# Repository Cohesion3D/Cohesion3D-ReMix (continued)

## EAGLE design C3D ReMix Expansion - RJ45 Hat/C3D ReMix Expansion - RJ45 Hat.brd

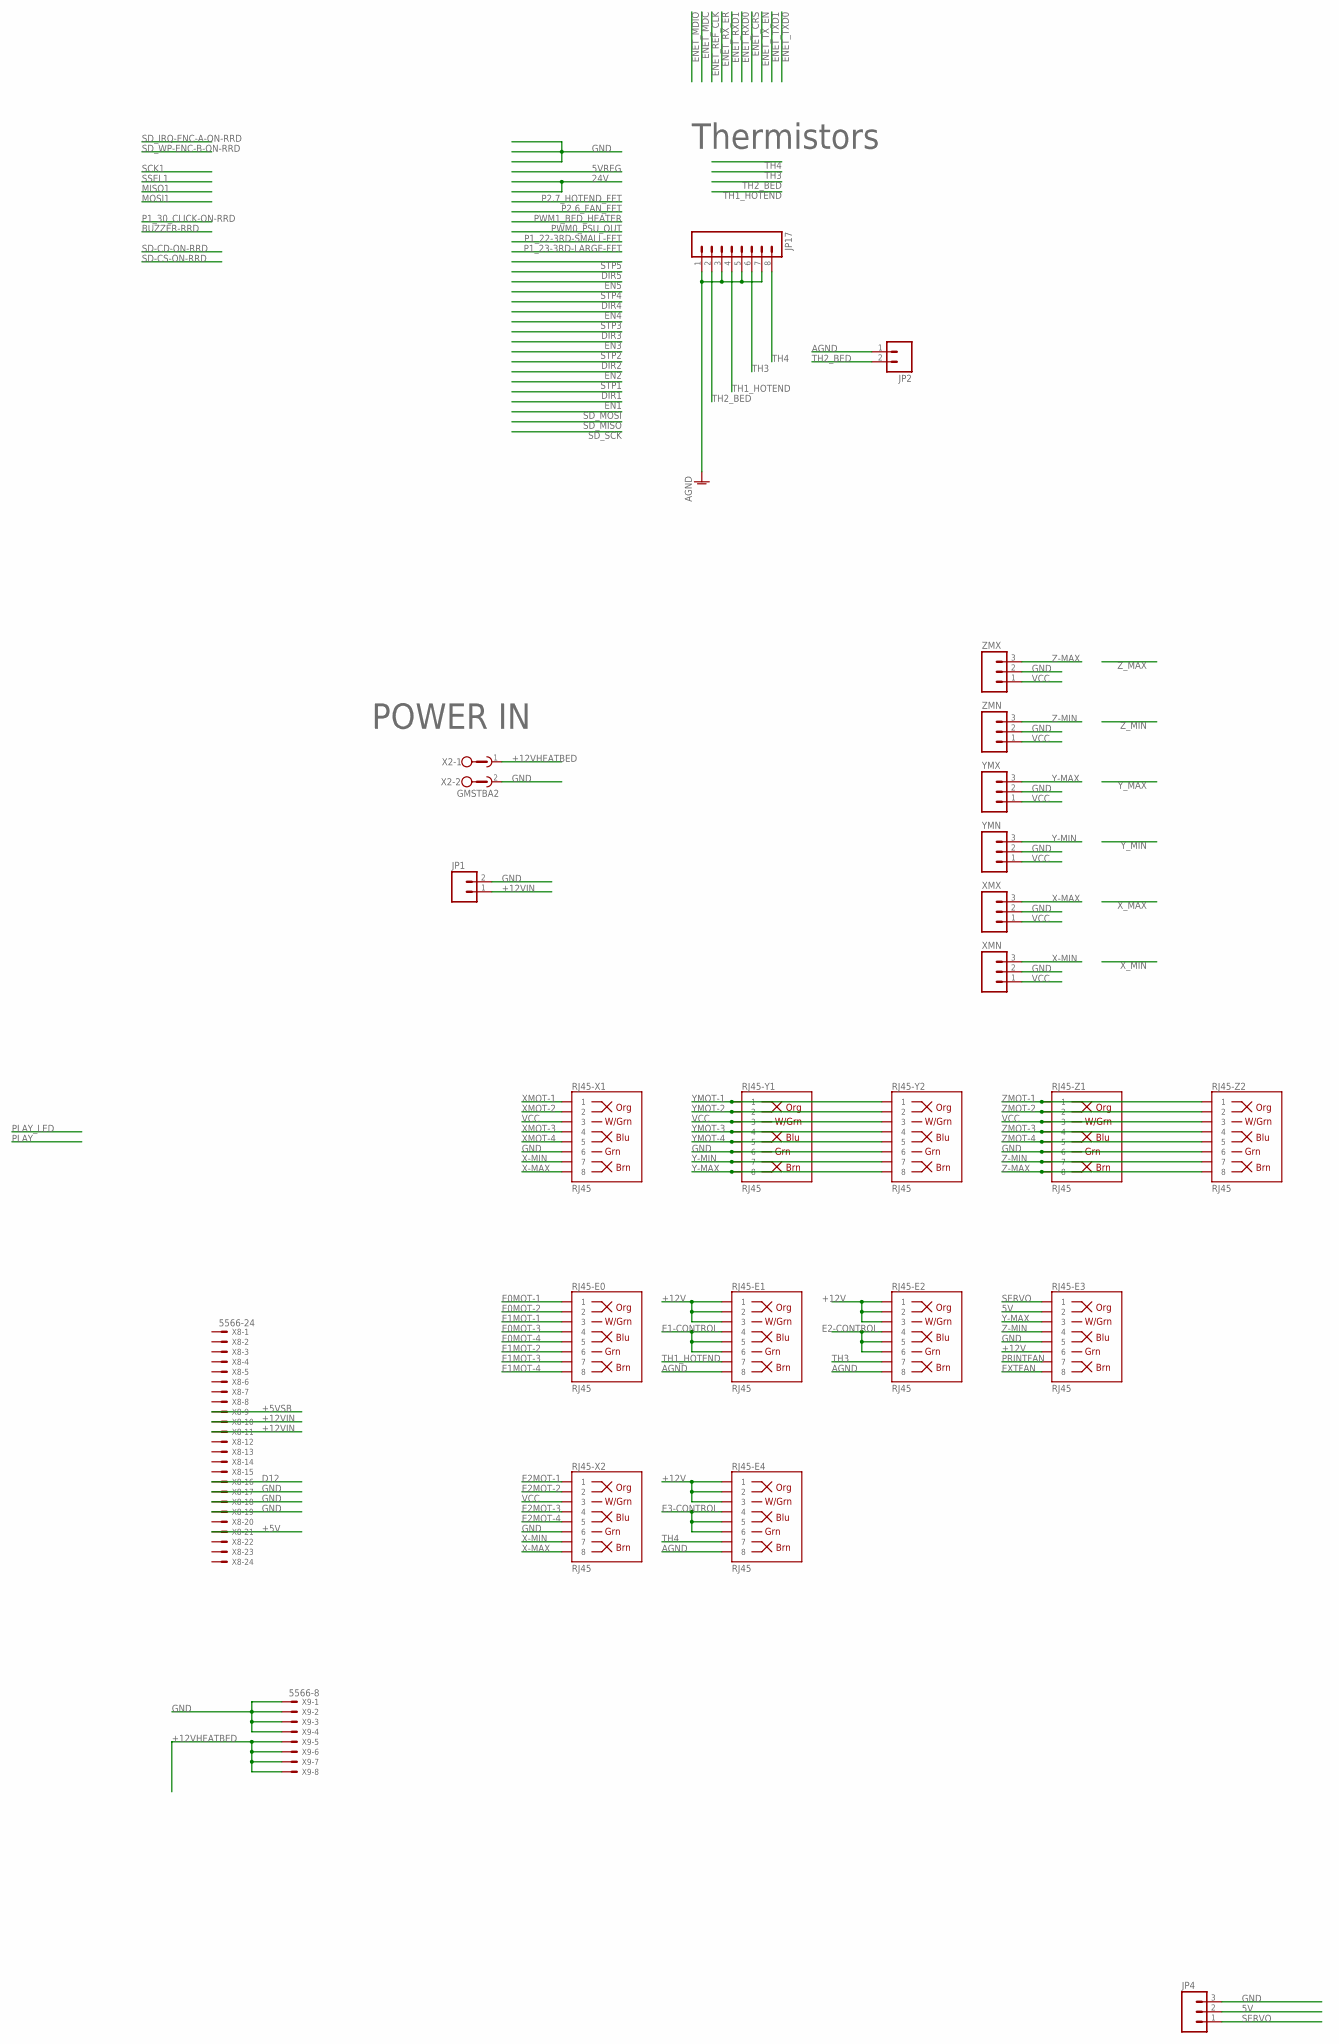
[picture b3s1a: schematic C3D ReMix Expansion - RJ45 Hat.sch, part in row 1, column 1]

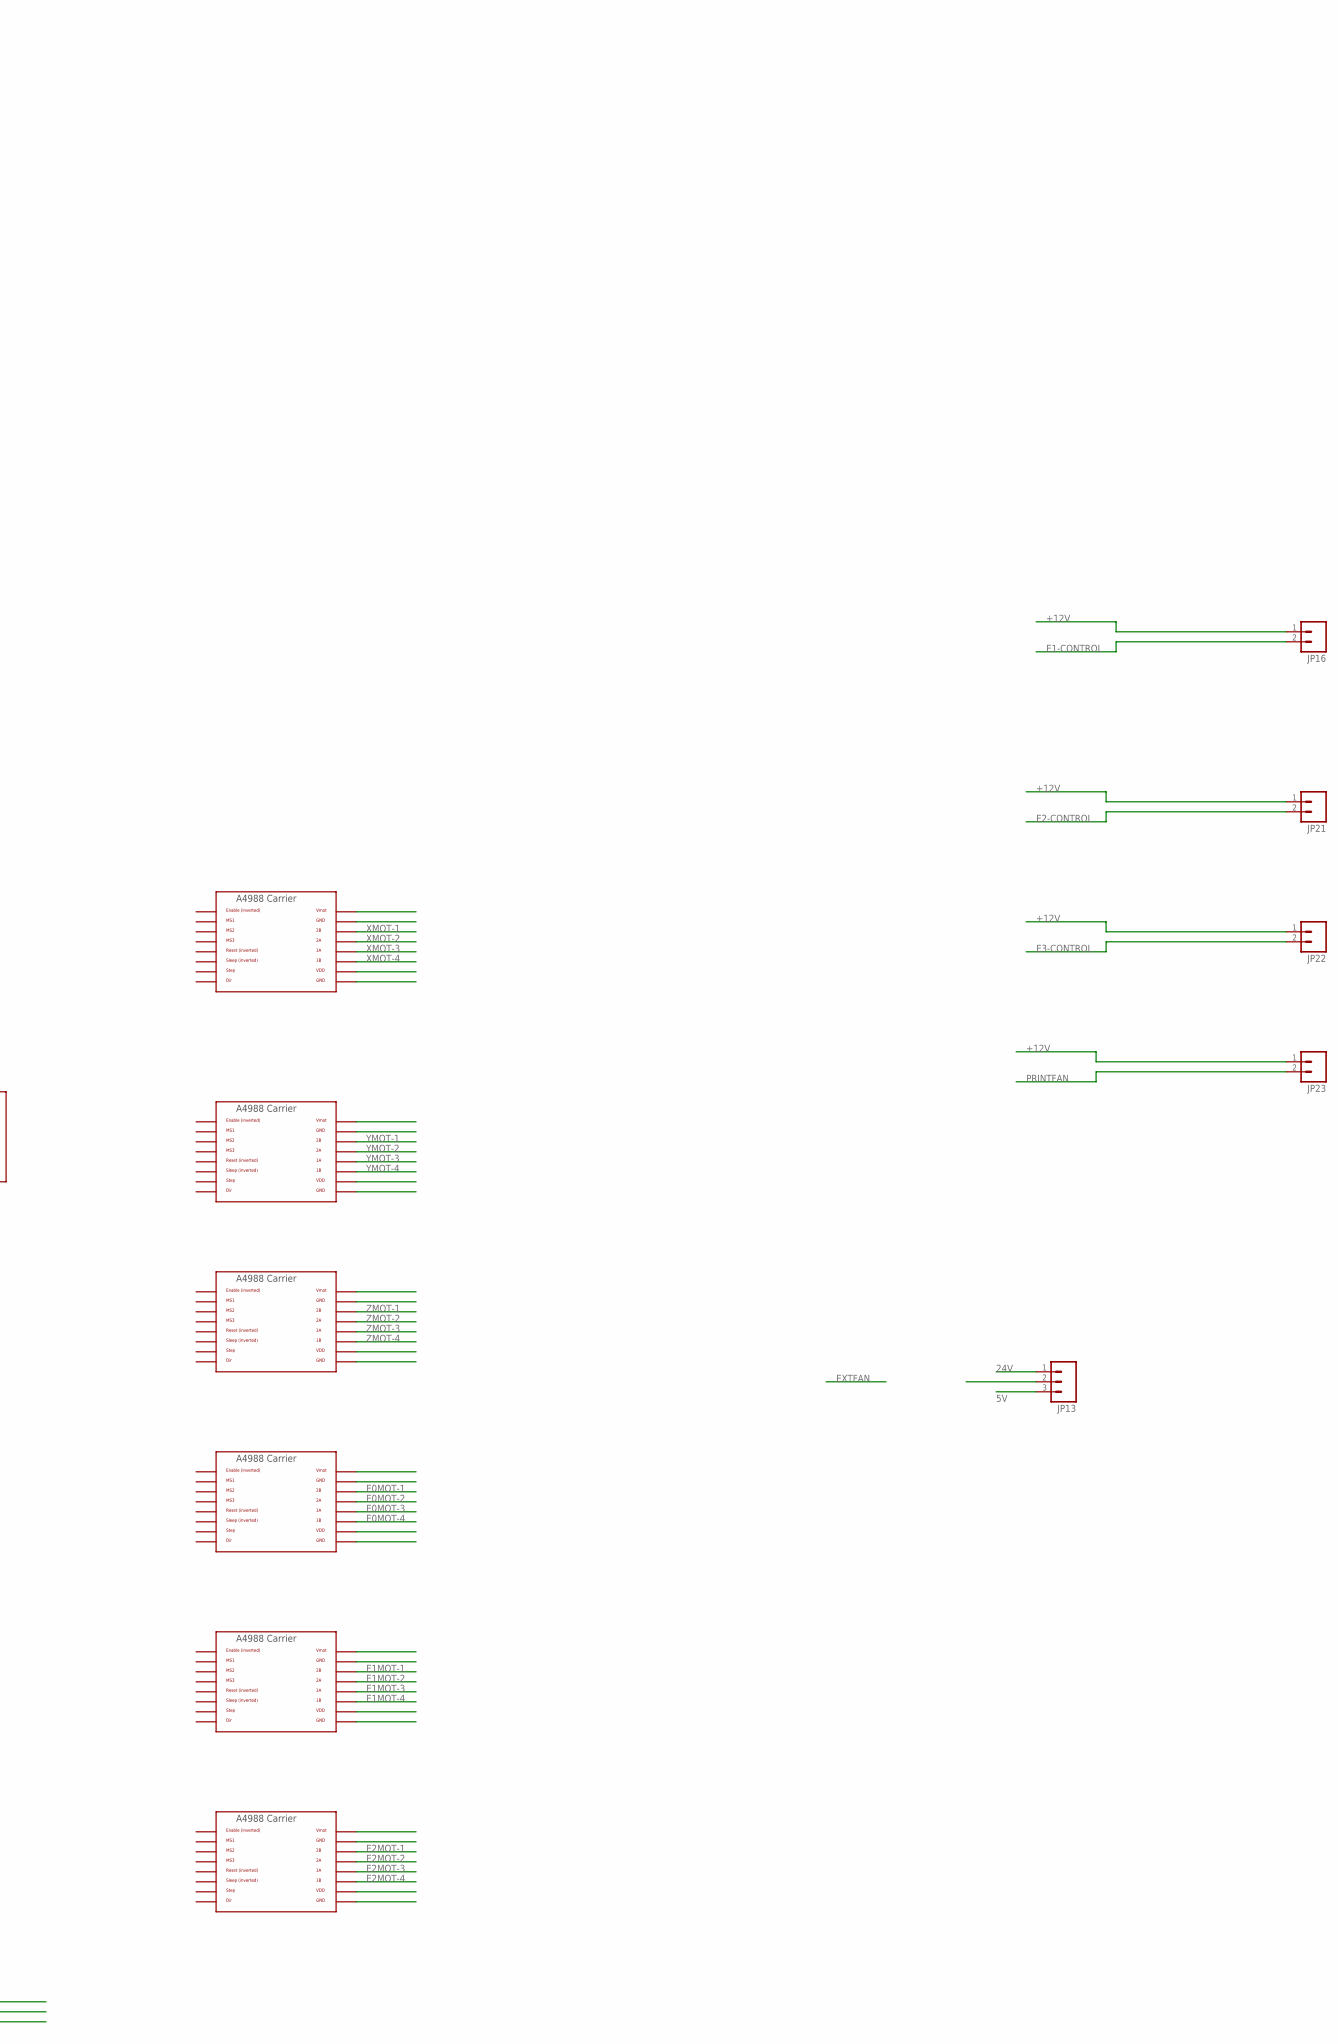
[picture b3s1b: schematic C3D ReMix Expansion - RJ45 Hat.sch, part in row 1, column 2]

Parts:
JP1: M025MM; SCREWTERMINAL-5MM-2
JP2, JP16, JP21, JP22, JP23: M02LOCK; 1X02_LOCK
JP4: M03LOCK; 1X03_LOCK
JP13: M03LOCK_NO_SILK; 1X03_LOCK_NO_SILK
JP17: M08LOCK; 1X08_LOCK
RJ45-E0, RJ45-E1, RJ45-E2, RJ45-E3, RJ45-E4, RJ45-X1, RJ45-X2, RJ45-Y1, RJ45-Y2, RJ45-Z1, RJ45-Z2: RJ45; RJ45-8
U$1, U$5, U$6, U$7, U$8, U$9: POLOLU_A4983CARRIER; A4988BREAKOUT
X2: GMSTBA2
X8: 5566-24
X9: 5566-8
XMN: M03POLAR_LOCK; MOLEX-1X3_LOCK
XMX: M03POLAR_LOCK; MOLEX-1X3_LOCK
YMN: M03POLAR_LOCK; MOLEX-1X3_LOCK
YMX: M03POLAR_LOCK; MOLEX-1X3_LOCK
ZMN: M03POLAR_LOCK; MOLEX-1X3_LOCK
ZMX: M03POLAR_LOCK; MOLEX-1X3_LOCK

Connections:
5V: JP4.2, JP13.3, RJ45-E3.2
24V: JP13.1
+5V: X8.21
+5VSB: X8.9
+12V: JP16.1, JP21.1, JP22.1, JP23.1, RJ45-E1.1, RJ45-E1.2, RJ45-E1.3, RJ45-E2.1, RJ45-E2.2, RJ45-E2.3, RJ45-E3.6, RJ45-E4.1, RJ45-E4.2, RJ45-E4.3
+12VHEATBED: X2.1, X9.5, X9.6, X9.7, X9.8
+12VIN: JP1.1, X8.10, X8.11
AGND: JP2.1, JP17.1, JP17.3, JP17.5, JP17.7, RJ45-E1.8, RJ45-E2.8, RJ45-E4.8
D12: X8.16
E0MOT-1: RJ45-E0.1, U$7.2B
E0MOT-2: RJ45-E0.2, U$7.2A
E0MOT-3: RJ45-E0.4, U$7.1A
E0MOT-4: RJ45-E0.5, U$7.1B
E1-CONTROL: JP16.2, RJ45-E1.4, RJ45-E1.5, RJ45-E1.6
E1MOT-1: RJ45-E0.3, U$8.2B
E1MOT-2: RJ45-E0.6, U$8.2A
E1MOT-3: RJ45-E0.7, U$8.1A
E1MOT-4: RJ45-E0.8, U$8.1B
E2-CONTROL: JP21.2, RJ45-E2.4, RJ45-E2.5, RJ45-E2.6
E2MOT-1: RJ45-X2.1, U$9.2B
E2MOT-2: RJ45-X2.2, U$9.2A
E2MOT-3: RJ45-X2.4, U$9.1A
E2MOT-4: RJ45-X2.5, U$9.1B
E3-CONTROL: JP22.2, RJ45-E4.4, RJ45-E4.5, RJ45-E4.6
EXTFAN: RJ45-E3.8
GND: JP1.2, JP4.3, RJ45-E3.5, RJ45-X1.6, RJ45-X2.6, RJ45-Y1.6, RJ45-Y2.6, RJ45-Z1.6, RJ45-Z2.6, X2.2, X8.17, X8.18, X8.19, X9.1, X9.2, X9.3, X9.4, XMN.2, XMX.2, YMN.2, YMX.2, ZMN.2, ZMX.2
PRINTFAN: JP23.2, RJ45-E3.7
SERVO: JP4.1, RJ45-E3.1
TH1_HOTEND: JP17.4, RJ45-E1.7
TH2_BED: JP2.2, JP17.2
TH3: JP17.6, RJ45-E2.7
TH4: JP17.8, RJ45-E4.7
VCC: RJ45-X1.3, RJ45-X2.3, RJ45-Y1.3, RJ45-Y2.3, RJ45-Z1.3, RJ45-Z2.3, XMN.1, XMX.1, YMN.1, YMX.1, ZMN.1, ZMX.1
X-MAX: RJ45-X1.8, RJ45-X2.8, XMX.3
X-MIN: RJ45-X1.7, RJ45-X2.7, XMN.3
XMOT-1: RJ45-X1.1, U$1.2B
XMOT-2: RJ45-X1.2, U$1.2A
XMOT-3: RJ45-X1.4, U$1.1A
XMOT-4: RJ45-X1.5, U$1.1B
Y-MAX: RJ45-E3.3, RJ45-Y1.8, RJ45-Y2.8, YMX.3
Y-MIN: RJ45-Y1.7, RJ45-Y2.7, YMN.3
YMOT-1: RJ45-Y1.1, RJ45-Y2.1, U$5.2B
YMOT-2: RJ45-Y1.2, RJ45-Y2.2, U$5.2A
YMOT-3: RJ45-Y1.4, RJ45-Y2.4, U$5.1A
YMOT-4: RJ45-Y1.5, RJ45-Y2.5, U$5.1B
Z-MAX: RJ45-Z1.8, RJ45-Z2.8, ZMX.3
Z-MIN: RJ45-E3.4, RJ45-Z1.7, RJ45-Z2.7, ZMN.3
ZMOT-1: RJ45-Z1.1, RJ45-Z2.1, U$6.2B
ZMOT-2: RJ45-Z1.2, RJ45-Z2.2, U$6.2A
ZMOT-3: RJ45-Z1.4, RJ45-Z2.4, U$6.1A
ZMOT-4: RJ45-Z1.5, RJ45-Z2.5, U$6.1B

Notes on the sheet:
Thermistors
POWER IN

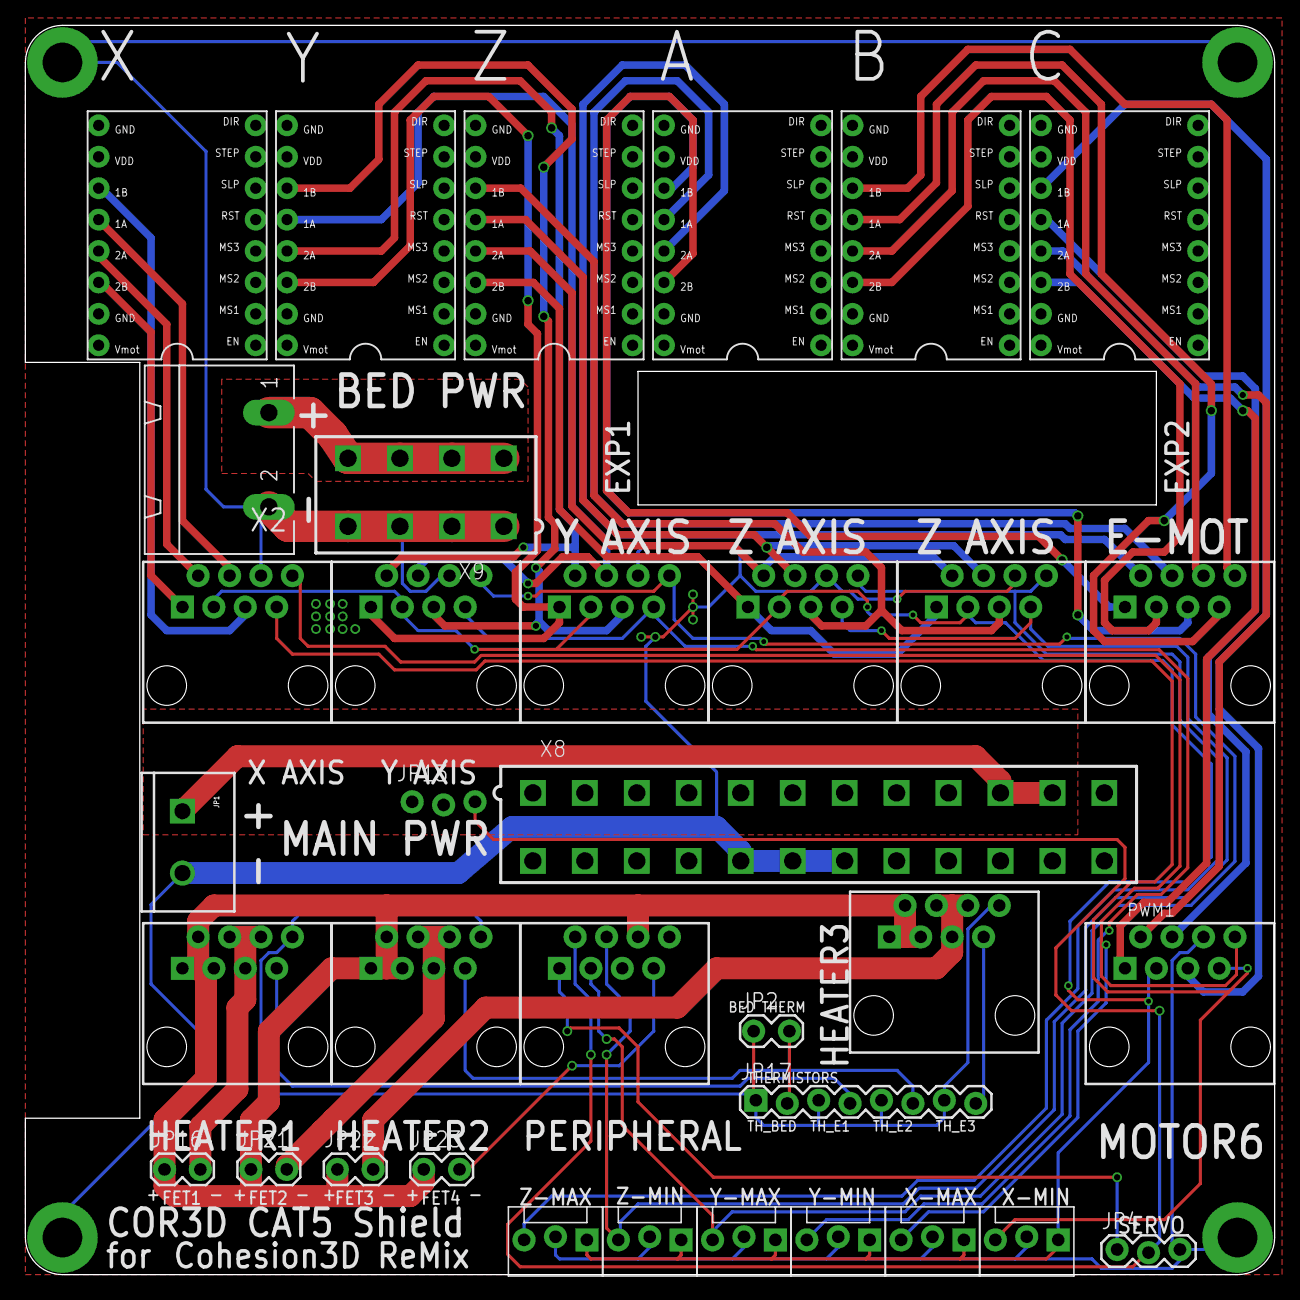
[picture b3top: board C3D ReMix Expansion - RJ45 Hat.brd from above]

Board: 2 copper layers, 101.0 x 101.0 mm, 35 parts (0 on the bottom side), 46 nets.

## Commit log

2016-05-31 Initial Commit of v0 board designs
2016-05-31 Cleaned up to all 8/8 mil specification. Woohoo!
2016-05-31 More cleanup. Changed 100u PTH to SMD
2016-05-31 Moved some MOSFET copper pours around
2016-05-31 Added VMOT indicator led
2016-06-01 More Cleanup. Added Headers to Mosfet outputs
2016-06-02 rev2 initial ready
2016-06-02 CAM-0 generated. Peer review time.
2016-06-02 Major routing cleanup per feedback from real engineer
2016-06-05 About to fix ethernet
2016-06-10 Almost done, but need to replace 220uF caps with SMD
2016-06-10 1/2 Cap 220uF Converted
2016-07-06 Rev2, Huge Amount of stuff added
